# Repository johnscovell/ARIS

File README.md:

# Project-ARIS
A collection of programs for sensor data processing, machine learning, GPS integration, and hub-to-hub communication in a distributed system. All files are in this Google Drive: https://drive.google.com/drive/folders/1TDeO9jrBaVlAoOB7IxtzkSROdyFAsIbH?usp=sharing. This GitHub does not contain all files - specifically for ARIS-Beacon Unity files.
# Project README

This README is a guide for navigating the many folders and files in this repository. Start at the top and work your way down the list. Importantly, read the NASA SUITS mission description to understand the concepts and intentions of the design. Here is our video: https://youtu.be/8anOoq1N8Tc?feature=shared. Here is the previous team's video: https://youtu.be/KLRMTx8ZErM?feature=shared.

1. **Project-ARIS-main**:
   - Created by the 2022-2023 team: Maryam Aminu Mukhtar, Oussama Ourich, Felice Gabardi, Kalvin Fonseca
   - Their report and code is provided, as well as system diagrams, PCB designs, etc.
   - Focus on Hub1 and Hub2 Pi codes - start with the sh files: Hub1.sh and Hub2.sh. These files execute the necessary Python scripts that allows for the sensor hubs to communicate, as well as initiating the machine learning.
   - Study the ML folder: ML.py and AR_Assistant.py scripts specifically, as well as their data sets.
   - There is server communication! Figure out how each sensor hubs communicate.
   
2. **CS682-ARIS-main**:
   - Created by CS graduate team of 2023: Parth Akre, Karthik Mukka, Pravallika Venkata
   - ARIS-Beacon is the Unity code for the HoloLens
   - LMCC_frontEnd is a template for a central control console for the system
   
3. **SunFounder_PiCar-V**:
   - SunFounder code to run the rover. We utilized the remote_control folder to make the rover move via a server
   - Your new rover will probably have updated code that actually works (we couldn't get the camera running)
   
4. **PCB**:
   - We started to design a PCB to replace the sensor hubs. This could be future work for your team.

-*Sal Baez (CE) Co-Team Lead, 
Fisseha Tegegne (EE) Co-Team Lead,
John Scovell (EE) Junior Member*

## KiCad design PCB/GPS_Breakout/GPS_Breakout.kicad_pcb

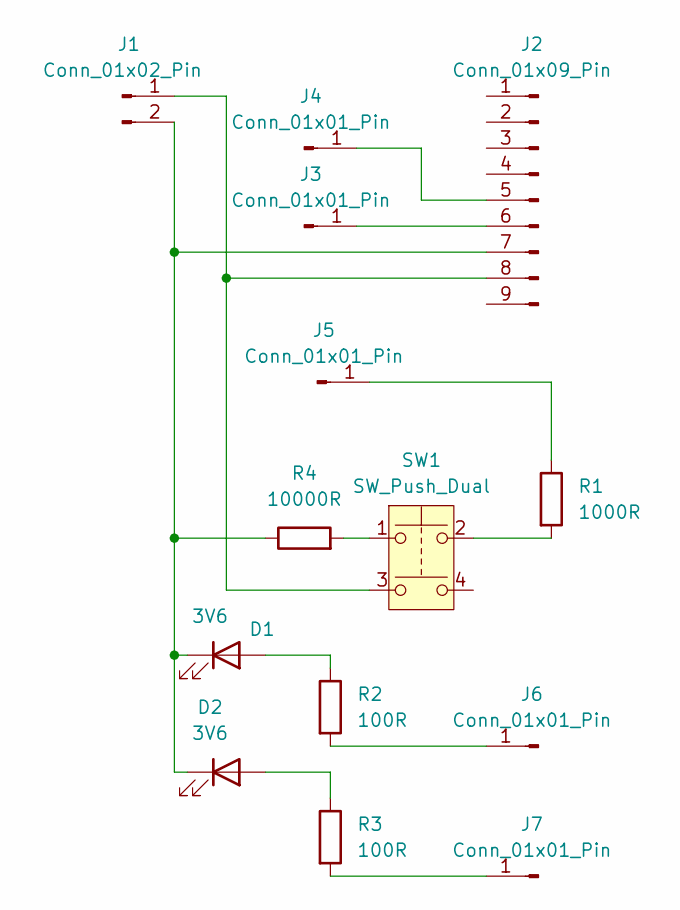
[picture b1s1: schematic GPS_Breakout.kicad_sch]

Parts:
D1, D2: 3V6; D_0201_0603Metric
J1: Conn_01x02_Pin; PinHeader_1x02_P1.27mm_Vertical
J2: Conn_01x09_Pin; PinHeader_1x09_P1.27mm_Vertical
J3, J4, J5, J6, J7: Conn_01x01_Pin; PinHeader_1x01_P1.27mm_Vertical
R1: 1000R; R_0805_2012Metric_Pad1.20x1.40mm_HandSolder
R2, R3: 100R; R_0805_2012Metric_Pad1.20x1.40mm_HandSolder
R4: 10000R; R_0805_2012Metric_Pad1.20x1.40mm_HandSolder
SW1: SW_Push_Dual; Push_E-Switch_KS01Q01

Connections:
unnamed: D1.2 (A), R2.1
unnamed: D1.1 (K), D2.1 (K), J1.2, J2.7, R4.1
unnamed: D2.2 (A), R3.1
unnamed: J1.1, J2.8, SW1.3
unnamed: J2.5, J4.1
unnamed: J2.6, J3.1
unnamed: J5.1, R1.1
unnamed: J6.1, R2.2
unnamed: J7.1, R3.2
unnamed: R1.2, SW1.2
unnamed: R4.2, SW1.1

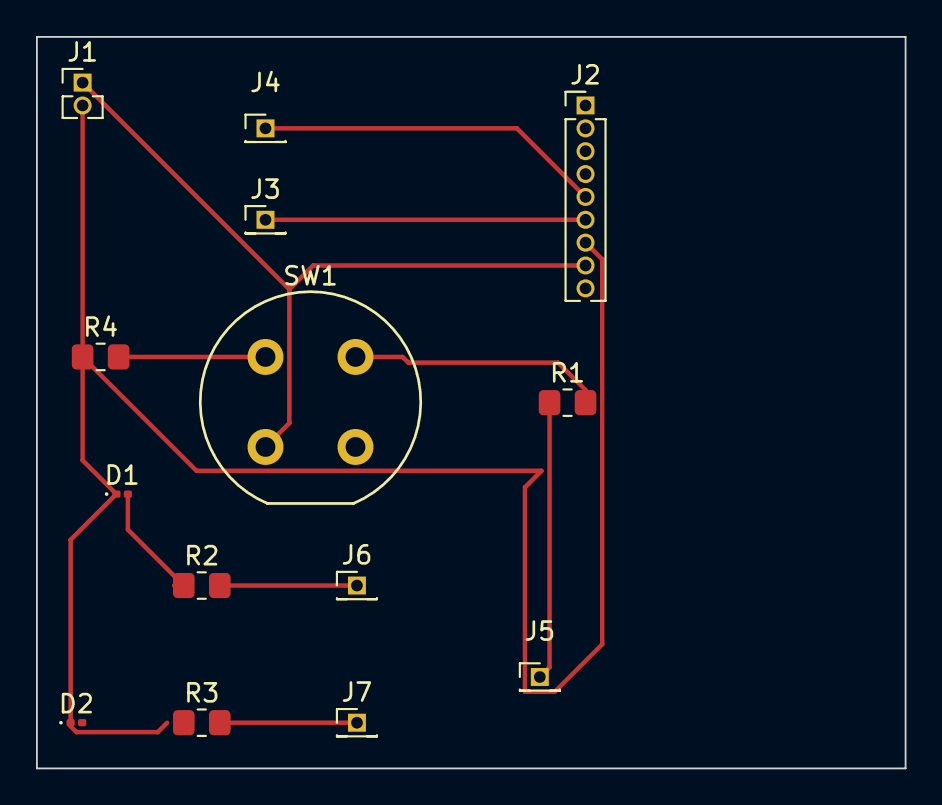
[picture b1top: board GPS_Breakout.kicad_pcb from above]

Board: 2 copper layers, 48.3 x 40.6 mm, 14 parts (0 on the bottom side), 11 nets.

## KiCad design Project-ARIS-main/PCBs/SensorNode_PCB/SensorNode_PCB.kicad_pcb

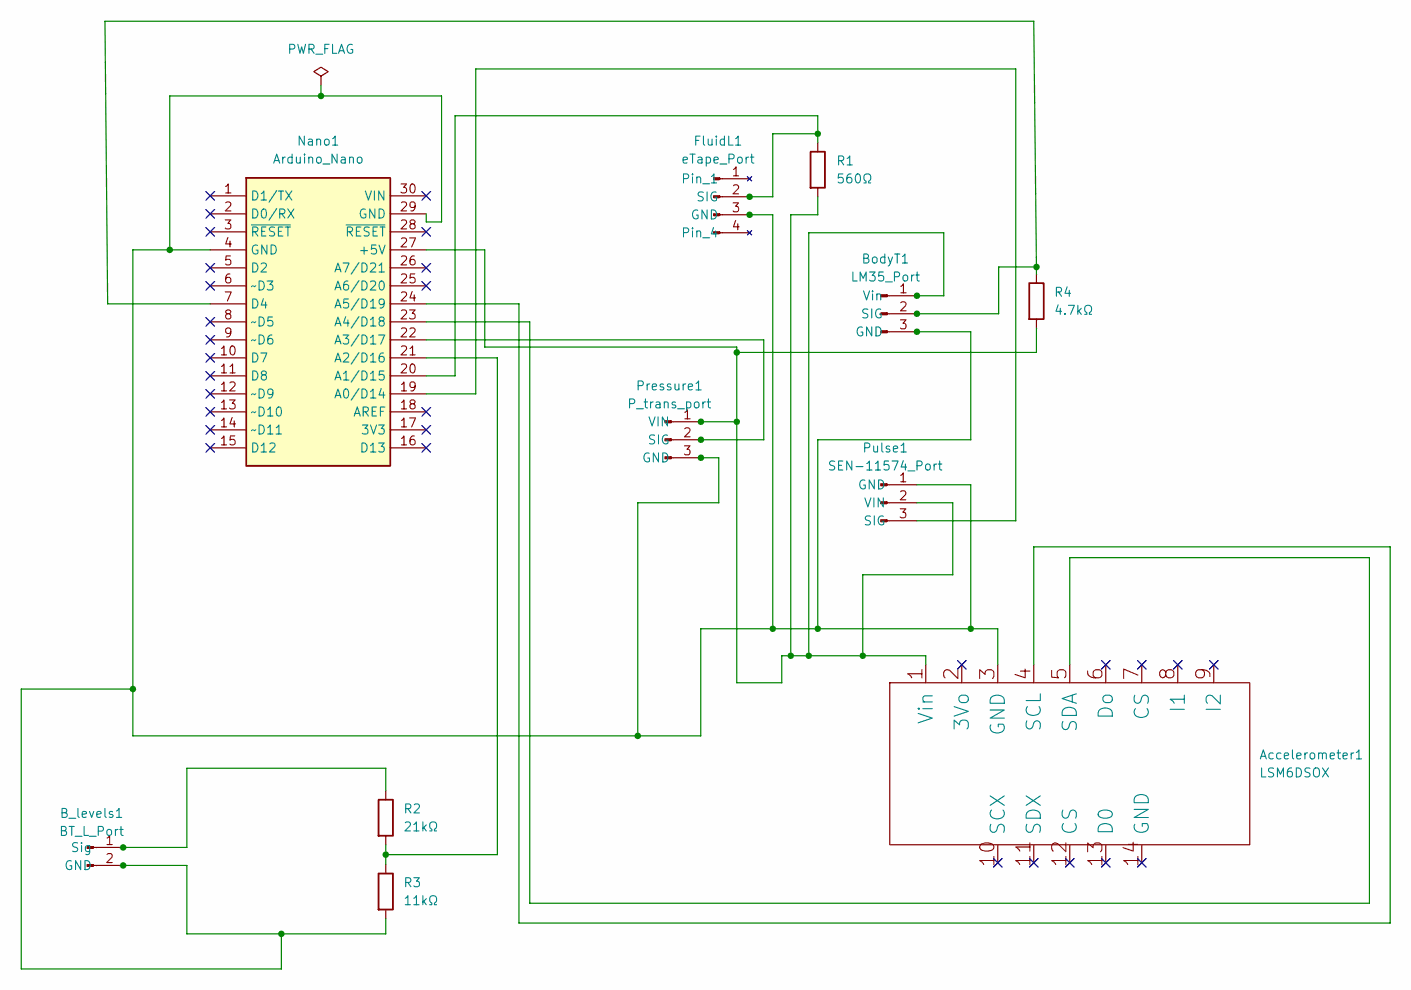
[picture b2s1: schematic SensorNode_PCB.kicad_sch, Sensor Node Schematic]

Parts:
Accelerometer1: LSM6DSOX
B_levels1: BT_L_Port; PinHeader_1x02_P2.54mm_Vertical
BodyT1: LM35_Port; PinHeader_1x03_P2.54mm_Vertical
FluidL1: eTape_Port; PinHeader_1x04_P2.54mm_Vertical
Nano1: Arduino_Nano
Pressure1: P_trans_port; PinHeader_1x03_P2.54mm_Vertical
Pulse1: SEN-11574_Port; PinHeader_1x03_P2.54mm_Vertical
R1: 560Ω; R_Axial_DIN0207_L6.3mm_D2.5mm_P7.62mm_Horizontal
R2: 21kΩ; R_Axial_DIN0207_L6.3mm_D2.5mm_P7.62mm_Horizontal
R3: 11kΩ; R_Axial_DIN0207_L6.3mm_D2.5mm_P7.62mm_Horizontal
R4: 4.7kΩ; R_Axial_DIN0207_L6.3mm_D2.5mm_P7.62mm_Horizontal

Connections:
unnamed: Accelerometer1.3 (GND), B_levels1.2 (GND), BodyT1.3 (GND), FluidL1.3 (GND), Nano1.4 (GND), Nano1.29 (GND), Pressure1.3 (GND), Pulse1.1 (GND), R3.2
unnamed: Accelerometer1.4 (SCL), Nano1.24 (A5/D19)
unnamed: Accelerometer1.5 (SDA), Nano1.23 (A4/D18)
unnamed: B_levels1.1 (Sig), R2.1
unnamed: FluidL1.2 (SIG), Nano1.20 (A1/D15), R1.1
unnamed: BodyT1.2 (SIG), Nano1.7 (D4), R4.1
unnamed: Nano1.19 (A0/D14), Pulse1.3 (SIG)
unnamed: Nano1.21 (A2/D16), R2.2, R3.1
unnamed: Nano1.22 (A3/D17), Pressure1.2 (SIG)
unnamed: Accelerometer1.1 (Vin), BodyT1.1 (Vin), Nano1.27 (+5V), Pressure1.1 (VIN), Pulse1.2 (VIN), R1.2, R4.2

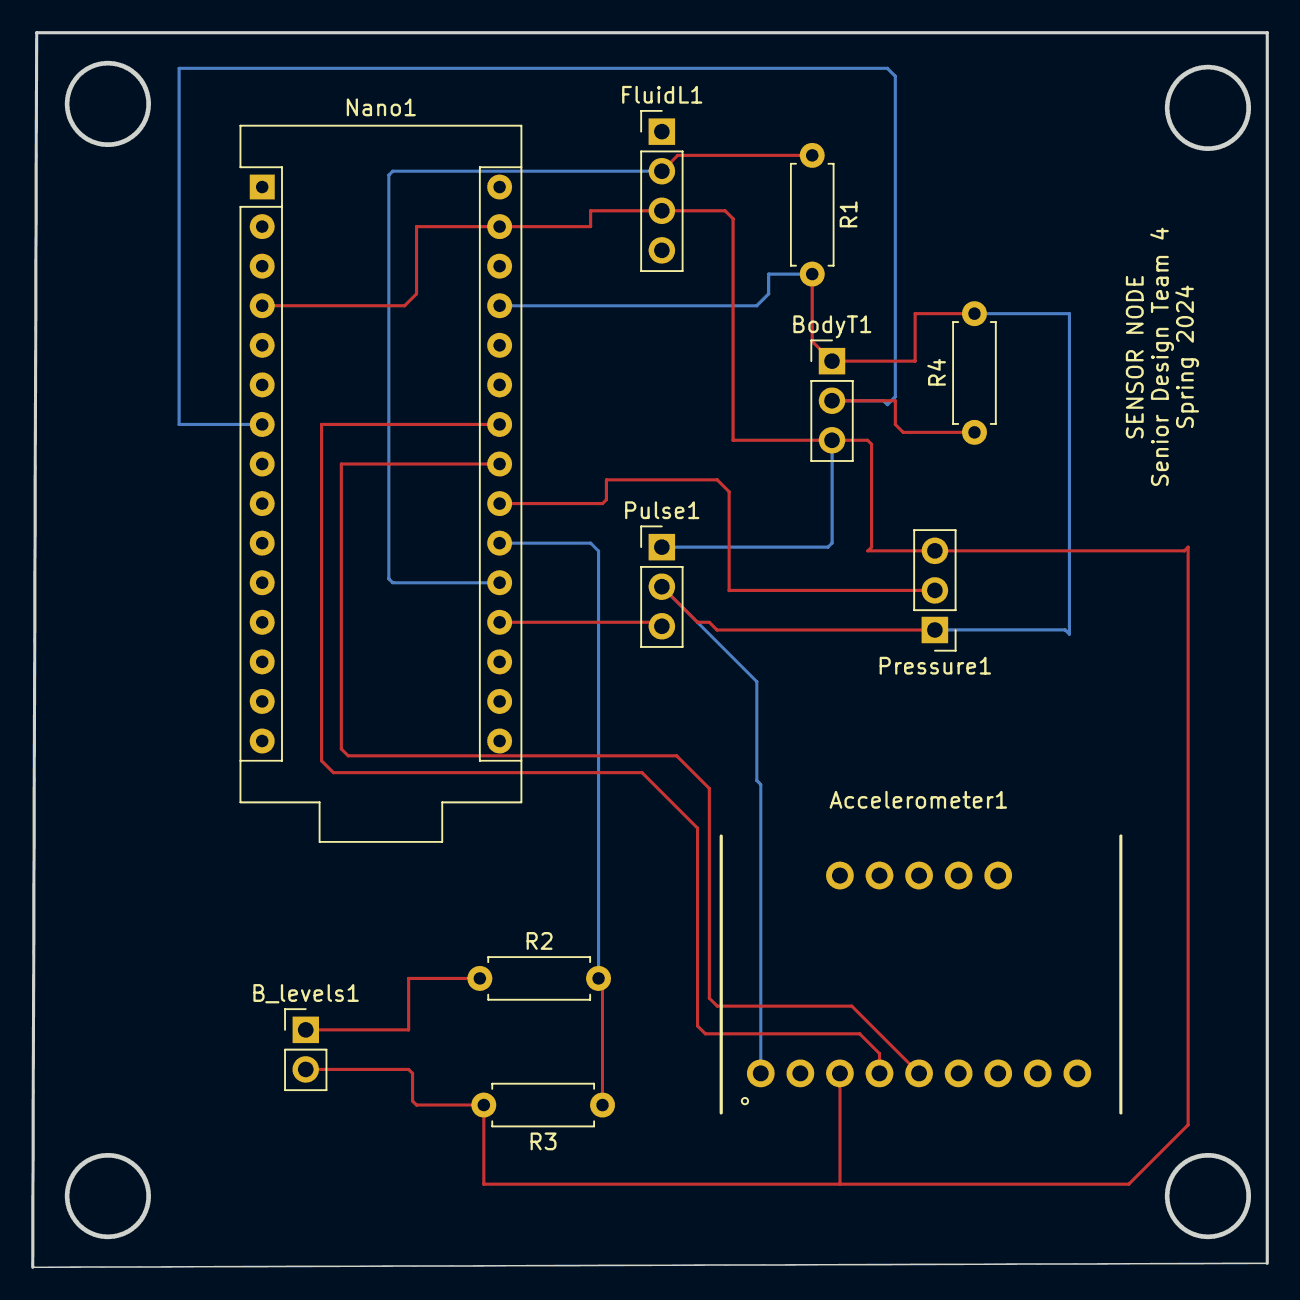
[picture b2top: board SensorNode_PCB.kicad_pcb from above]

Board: 2 copper layers, 79.2 x 79.2 mm, 11 parts (0 on the bottom side), 10 nets.

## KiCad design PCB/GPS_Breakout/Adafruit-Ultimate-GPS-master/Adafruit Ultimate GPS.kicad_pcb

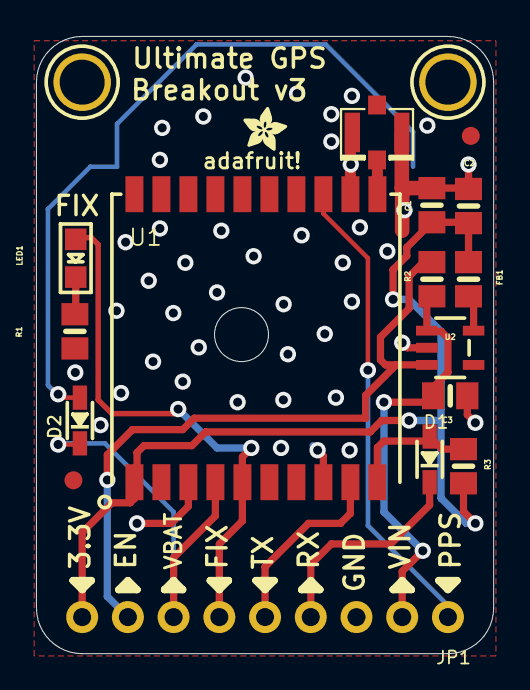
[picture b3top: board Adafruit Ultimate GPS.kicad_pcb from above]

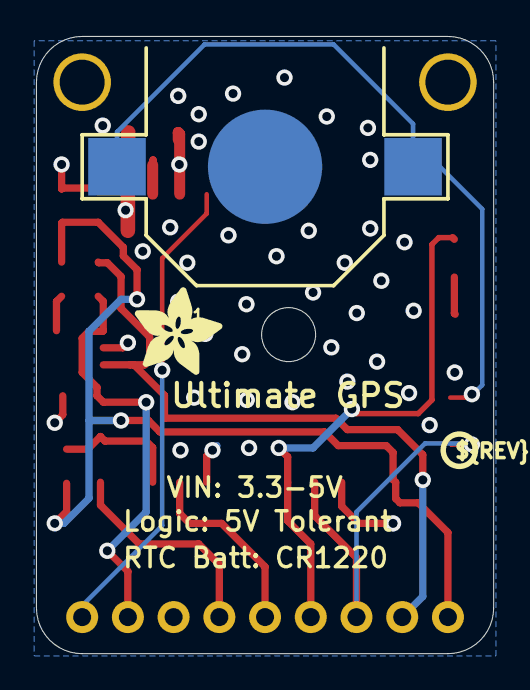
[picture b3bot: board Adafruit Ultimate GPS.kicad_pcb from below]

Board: 2 copper layers, 25.4 x 34.3 mm, 22 parts (3 on the bottom side), 14 nets.

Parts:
B1: CR1220
C1: 0.1uF; 0805-NO
C2, C3: 10uF; 0805-NO
D1: 1N4148; SOD-323
D2: CUS520; SOD-323
FB1: Ferrite; 0805-NO
FID1, FID2: FIDUCIAL""; FIDUCIAL_1MM
JP1: 1X09_ROUND_70
LED1: RED; CHIPLED_0805
R1: 1K; 0805-NO
R2, R3: 10K; 0805-NO
U1: FGPMMOPA6H
U2: MIC5225-3.3; SOT23-5
U$8, U$9: MOUNTINGHOLE2.5; MOUNTINGHOLE_2.5_PLATED
U$15: ADAFRUIT_2.5MM
U$16: PCBFEAT-REV-040
U$18: ADAFRUIT_5MM
U$20: U.FL

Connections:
1PPS: JP1.1, U1.P$13
3.3V: C1.1, C2.1, FB1.2, JP1.9, R3.1, U1.P$1
ENABLE: JP1.8, R2.1, U2.3
FIX: JP1.6, LED1.A, U1.P$5
GND: B1.-, C1.2, C2.2, C3.2, JP1.3, R1.1, U1.P$3, U1.P$8, U1.P$12, U1.P$19, U2.2, U$20.P$1, U$20.P$2
unnamed: B1.+$1, B1.+$2, D2.A
unnamed: LED1.C, R1.2
unnamed: FB1.1, U2.5
unnamed: U1.P$11, U$20.P$3
RX: D1.C, JP1.4
RX_3V: D1.A, R3.2, U1.P$10
TX: JP1.5, U1.P$9
VBACKUP: D2.C, JP1.7, U1.P$4
VIN: C3.1, JP1.2, R2.2, U2.1
